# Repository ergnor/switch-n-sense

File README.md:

# Switch-N-Sense
This is a Kicad redesign of switch-n-sense pcb from LibreSolar project

## Design changes:

* Wire to board connector is replaced with cheaper alternative - Keystone 8197 (30A rating)
* MOSFET's footprint now is TDSON-8-1 for 5x6 mm SMD transistors 
* Pinout of connector to the BMS (IDC connector) is compatible with previous version of pcb
* C1,C2,C6 and C7 are changed to 0805(2012) size

## Current target

Current rating can be adjusted depending on chosen MOSFETs and sense resistors, but major limiting factor is connector (30A)

| MOSFET (2x)   | Voltage | Maximum Current | Remark                                       |
|---------------|---------|-----------------|----------------------------------------------|
|NVMFS6H800NT1G | 48V     | 30 A            | connector limited                            |

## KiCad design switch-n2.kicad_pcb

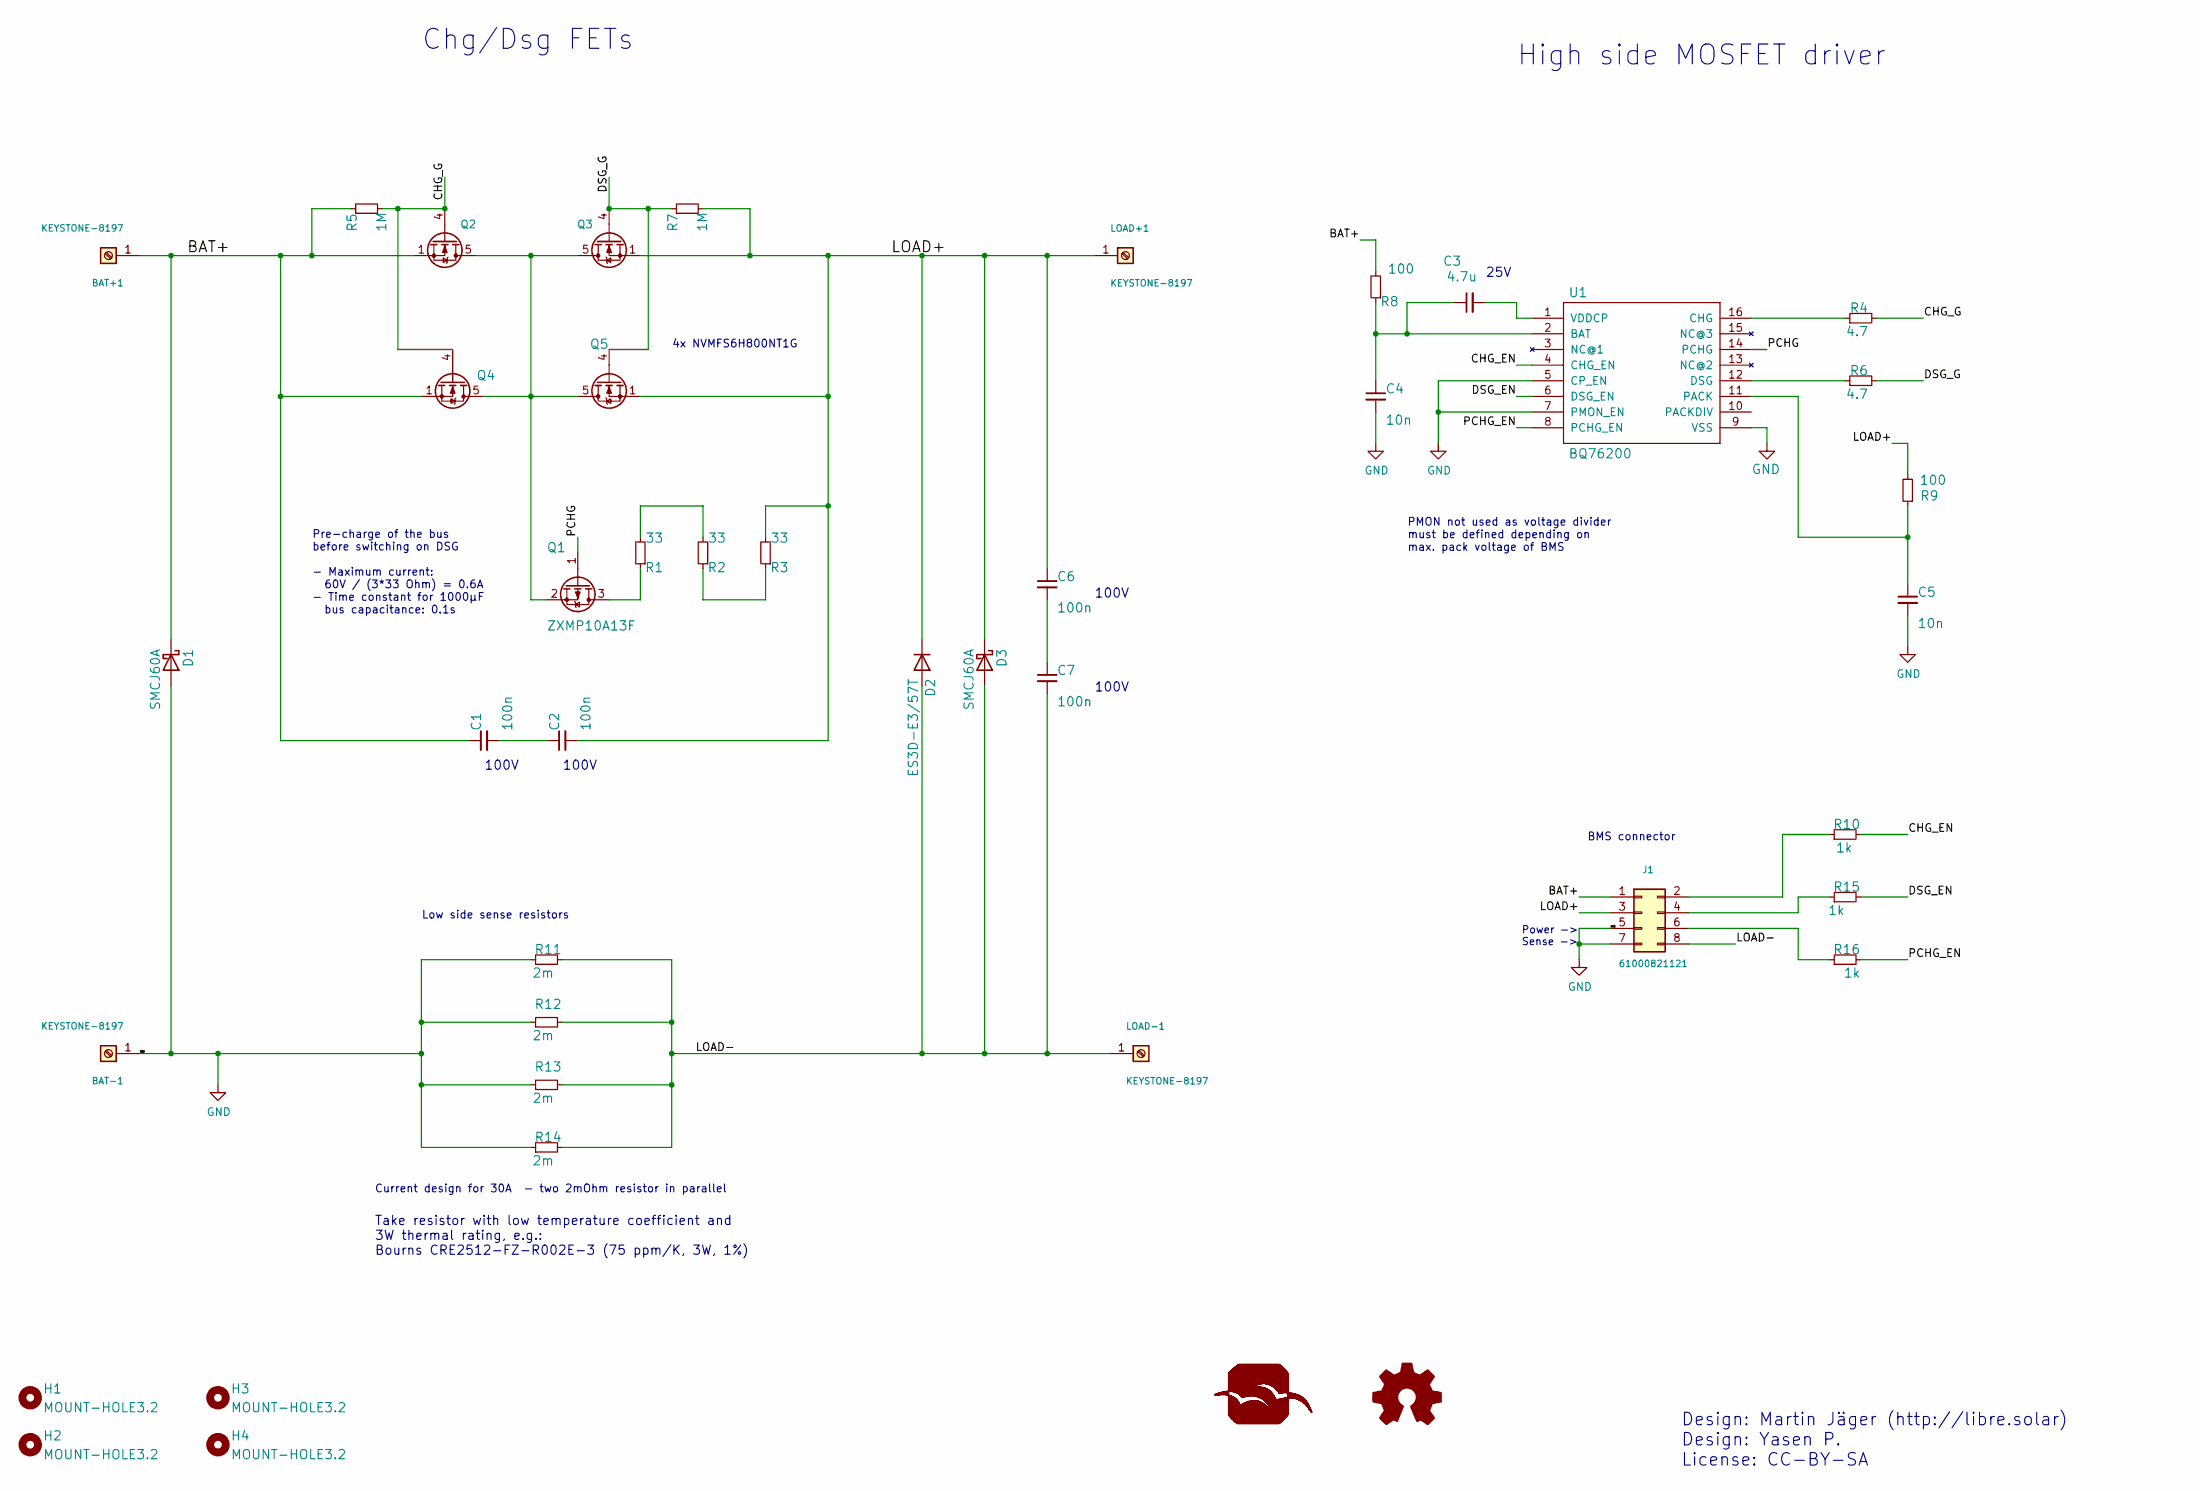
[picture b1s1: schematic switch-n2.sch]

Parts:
BAT+1: KEYSTONE-8197; 8197
BAT-1: KEYSTONE-8197; 8197
C1, C2, C6, C7: 100n; C_0805_2012Metric; MPN 0603B104K500CT
C3: 4.7u; C_0805_2012Metric; MPN 0603B104K500CT
C4, C5: 10n; C_0603_1608Metric; MPN GRM188R71H103KA01D.
D1, D3: SMCJ60A; D_SMC; MPN SMCJ75A
D2: ES3D-E3/57T; D_SMC; MPN ES3D-E3/57T.
H1, H2, H3, H4: MOUNT-HOLE3.2; MountingHole_3.2mm_M3_ISO14580_Pad
J1: 61000821121; PinHeader_2x04_P2.54mm_Vertical_SMD
LOAD+1: KEYSTONE-8197; 8197
LOAD-1: KEYSTONE-8197; 8197
N1: OSHW-LOGOM; OSHW-LOGO-M
Q1: ZXMP10A13F; SOT-23; MPN ZXMP10A13FTA
Q2, Q3, Q4, Q5: NVMFS6H800NT1G; TDSON-8-1
R1, R2, R3: 33; R_2010_5025Metric; MPN ASC2010-33RFT4
R4, R6: 4.7; R_0603_1608Metric; MPN ERJU06F1004V
R5, R7: 1M; R_0603_1608Metric; MPN ERJU06F1004V
R8, R9: 100; R_0603_1608Metric; MPN MCMR06X1001FTL
R10, R15, R16: 1k; R_0603_1608Metric; MPN ERJU06F1004V
R11, R12, R13, R14: 2m; R_2512_6332Metric
U1: BQ76200; TSSOP16
U$1: LIBRESOLAR_LOGO

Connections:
/BAT+: BAT+1.1, C1.1, D1.1 (K), J1.1, Q2.1 (S), Q2.2 (S), Q2.3 (S), Q4.1 (S), Q4.2 (S), Q4.3 (S), R5.1, R8.2
/CHG_EN: R10.2, U1.4 (CHG_EN)
/CHG_G: Q2.4 (G), Q4.4 (G), R4.2, R5.2
/DSG_EN: R15.2, U1.6 (DSG_EN)
/DSG_G: Q3.4 (G), Q5.4 (G), R6.2, R7.1
/LOAD+: C2.2, C6.1, D2.1 (K), D3.1 (K), J1.3, LOAD+1.1, Q3.1 (S), Q3.2 (S), Q3.3 (S), Q5.1 (S), Q5.2 (S), Q5.3 (S), R3.2, R7.2, R9.2
/LOAD-: C7.2, D2.2 (A), D3.2 (A), J1.8, LOAD-1.1, R11.2, R12.2, R13.2, R14.2
/PCHG: Q1.1 (G), U1.14 (PCHG)
/PCHG_EN: R16.2, U1.8 (PCHG_EN)
GND: BAT-1.1, C4.2, C5.2, D1.2 (A), J1.5, J1.7, R11.1, R12.1, R13.1, R14.1, U1.5 (CP_EN), U1.7 (PMON_EN), U1.9 (VSS)
unnamed: C1.2, C2.1
unnamed: C3.1, C4.1, R8.1, U1.2 (BAT)
unnamed: C3.2, U1.1 (VDDCP)
unnamed: C5.1, R9.1, U1.11 (PACK)
unnamed: C6.2, C7.1
unnamed: J1.2, R10.1
unnamed: J1.4, R15.1
unnamed: J1.6, R16.1
unnamed: Q1.2 (S), Q2.5 (D), Q3.5 (D), Q4.5 (D), Q5.5 (D)
unnamed: Q1.3 (D), R1.1
unnamed: R1.2, R2.2
unnamed: R2.1, R3.1
unnamed: R4.1, U1.16 (CHG)
unnamed: R6.1, U1.12 (DSG)

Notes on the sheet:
Pre-charge of the bus before switching on DSG - Maximum current: 60V / (3*33 Ohm) = 0.6A - Time constant for 1000µF bus capacitance: 0.1s
Chg/Dsg FETs
High side MOSFET driver
Design: Martin Jäger (http://libre.solar) Design: Yasen P. License: CC-BY-SA
4x NVMFS6H800NT1G
Take resistor with low temperature coefficient and 3W thermal rating, e.g.: Bourns CRE2512-FZ-R002E-3 (75 ppm/K, 3W, 1%)
Low side sense resistors
BMS connector
Power -> Sense ->
PMON not used as voltage divider must be defined depending on max. pack voltage of BMS
100V
25V
Current design for 30A - two 2mOhm resistor in parallel

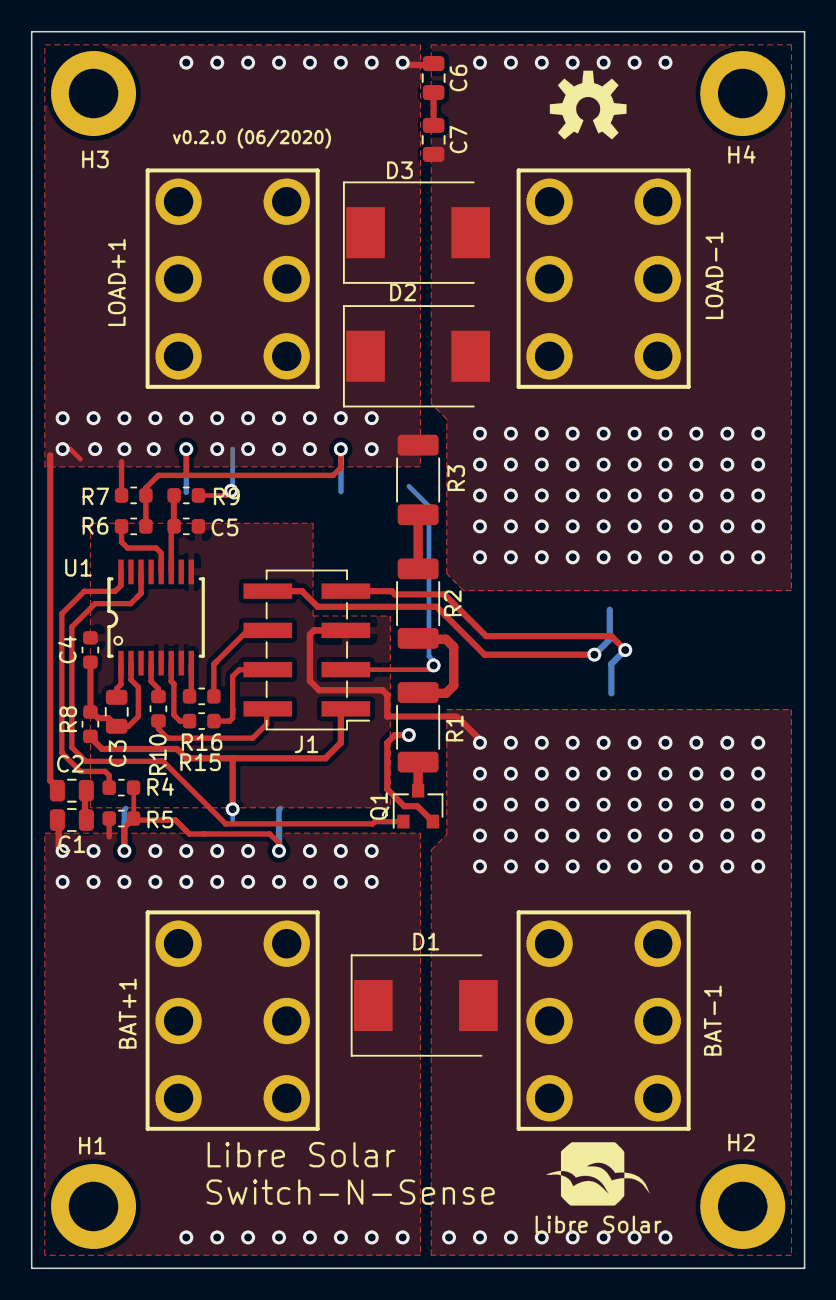
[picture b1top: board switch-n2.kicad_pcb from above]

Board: 2 copper layers, 50.0 x 80.0 mm, 43 parts (0 on the bottom side), 24 nets.

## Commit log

2020-06-28 my snapshot
2020-06-30 Fixed some comments on schematic
2020-07-01 Clean up schematics and add pdf version
